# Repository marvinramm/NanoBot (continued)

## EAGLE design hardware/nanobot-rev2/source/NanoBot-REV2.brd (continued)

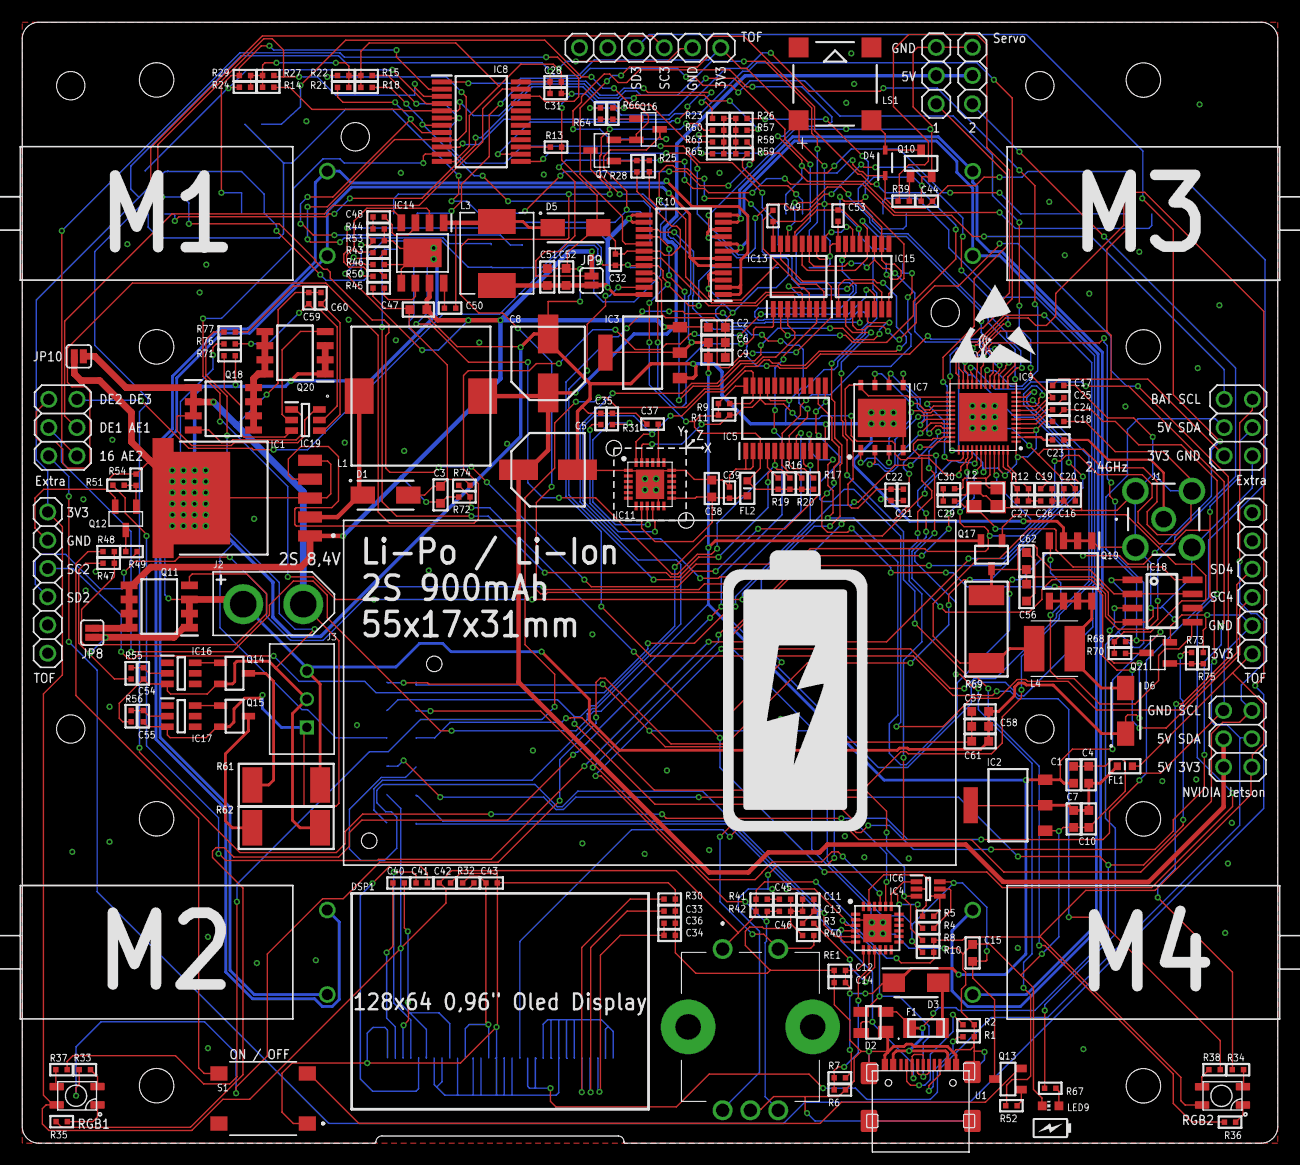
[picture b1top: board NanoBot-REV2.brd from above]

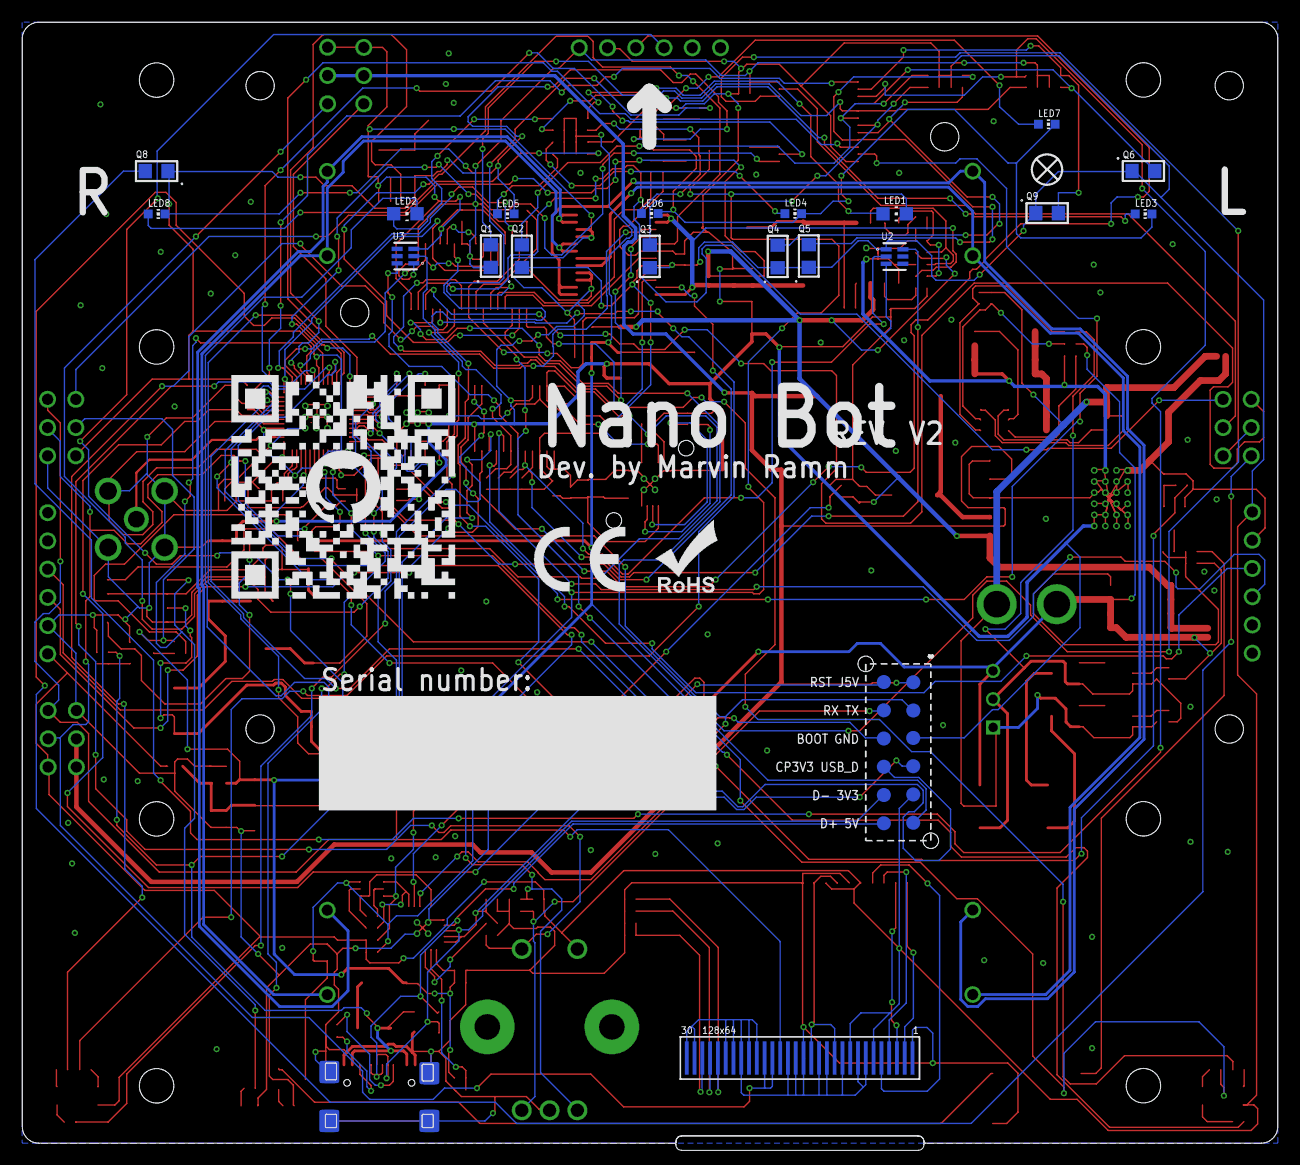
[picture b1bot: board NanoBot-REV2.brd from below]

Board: 2 copper layers, 112.9 x 100.8 mm, 240 parts (31 on the bottom side), 173 nets.

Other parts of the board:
U$3: JETSON_NANO

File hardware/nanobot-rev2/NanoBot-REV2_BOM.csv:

designators,description,manufacturer_part,lcsc_part,qty_per_board,link
U1,USB Connector,TYPE-C-31-M-31,C2760486,1,https://www.lcsc.com/product-detail/USB-Connectors_Korean-Hr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
F1,6V 1.5A 100A 3A 1206 Resettable Fuse,TLC-NSMD150,C261956,1,https://www.lcsc.com/product-detail/Resettable-Fuses_span-st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
D3,30V 550mV@5A 5A DO-221AC Schottky Barrier Diode,SK53AFL-TP,C780074,1,
D2,ESD protection,SP0503BAHTG,C7074,1,https://www.lcsc.com/product-detail/TVS_Littelfuse-SP0503BAH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
IC2,Linear Voltage Regulators 1A 60dB@(120Hz),AMS1117-3.3,C347222,1,https://www.lcsc.com/product-detail/Linear-Voltage-Regulator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
"FL1, FL2",50mΩ ±25% 120Ω@100MHz 0603 Ferrite Beads ROHS,BLM18PG121SN1D,C14709,2,https://www.lcsc.com/product-detail/Ferrite-Beads_Murata-Ele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
IC3,1.4A Fixed 5V~5V Positive 18V SOT-223 Linear Voltage Regulators (LDO) ROHS,AMS1117-5.0,C473812,1,https://www.lcsc.com/product-detail/Linear-Voltage-Regulator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
"D1, D5, D6",40V Single 500mV@3A 3A SMA(DO-214AC) Schottky Barrier Diodes (SBD) ROHS,SS34A,C2886580,3,https://www.lcsc.com/product-detail/Schottky-Barrier-Diodes-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
IC1,TO-263-5 DC-DC Converters ROHS,LM2576S-5.0,C2920854,1,https://www.lcsc.com/product-detail/DC-DC-Converters_Minos-L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
IC5,TSSOP-24 Signal Switches / Encoders & Decoders / Multiplexers ROHS,TCA9548APWR,C130026,1,https://www.lcsc.com/product-detail/Signal-Switches-Encoders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
L1,"1.9A 100uH ±20% SMD,12.5x12.5mm Power Inductors ROHS",SLF12575T-101M1R9-PF,C81470,1,https://www.lcsc.com/product-detail/Power-Inductors_TDK-SLF1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
IC4,QFN-24-EP(4x4) USB ICs ROHS,CP2102N-A02-GQFN24R,C969151,1,https://www.lcsc.com/product-detail/USB-ICs_SILICON-LABS-CP2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
IC6,"40V 150mW 100@10mA,1V 200mA 2 NPN SC-88 Bipolar Transistors - BJT ROHS",LMBT3904DW1T1G,C131781,1,https://www.lcsc.com/product-detail/Bipolar-Transistors-BJT_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
IC8,SSOP-24-208mil Analog Switches / Multiplexers ROHS,CD74HC4067SM96,C98457,1,https://www.lcsc.com/product-detail/Analog-Switches-Multiple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
IC7,WSON-8-EP(5x6) NOR FLASH ROHS,W25Q128JVPIQ,C2803379,1,https://www.lcsc.com/product-detail/NOR-FLASH_Winbond-Elec-W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
J1,1 Inner bore SMA Board Edge Positive foot 6GHz -65℃~+165℃ 50Ω 6.35mm Plugin RF Connectors / Coaxial Connectors ROHS,5-1814832-2,C482015,1,https://www.lcsc.com/product-detail/RF-Connectors-Coaxial-Co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
IC9,QFN-48-EP(6x6) RF Transceiver ICs ROHS,ESP32-D0WDQ6,C129733,1,https://www.lcsc.com/product-detail/RF-Transceiver-ICs_Espre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
L2,40MHz 12pF ±10ppm SMD3225-4P Crystals ROHS,S3240000121040,C426989,1,https://www.lcsc.com/product-detail/Crystals_JGHC-S324000012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
"Q1, Q2, Q3, Q4, Q5, Q6, Q8, Q9",20mA NPN 30V 100nA 940nm 0805 Phototransistors ROHS,PT17-21C/L41/TR8,C100090,8,https://www.lcsc.com/product-detail/Phototransistors_Everlig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
"U2, U3",Ambient Light Sensors ROHS,TCS34725FN,C2649487,2,https://www.lcsc.com/product-detail/Ambient-Light-Sensors_Ad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
"Q7, Q12, Q16, Q21","20V 2.9A 57mΩ@4.5V,3.6A 710mW N Channel SOT-23 MOSFETs ROHS",SI2302DDS-T1-GE3,C194092,4,https://www.lcsc.com/product-detail/MOSFETs_Vishay-Intertech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
"LED1, LED2",2600K~3200K White light 80mW 0805 Light Emitting Diodes (LED) ROHS,BZ-C0805-W2-E1,C2833071,2,https://www.lcsc.com/product-detail/Light-Emitting-Diodes-LE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
IC10,1A Brush DC Motor 2.7V~5.5V Parallel SSOP-24 Motor Driver ICs ROHS,"TB6612FNG,C,8,EL",C141517,1,https://www.lcsc.com/product-detail/Motor-Driver-ICs_TOSHIBA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
IC11,QFN-24-EP(4x4) Attitude Sensor/Gyroscope ROHS,MPU-6050,C24112,1,https://www.lcsc.com/product-detail/Attitude-Sensor-Gyroscop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
RE1,Plugin Rotary Encoders ROHS,PEC12R-4120F-S0012,C143801,1,https://www.lcsc.com/product-detail/Rotary-Encoders_BOURNS-P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
LS1,"Externally Driven 85dB@3.6V,10cm Magnetic 3.6V 2731Hz SMD,7.5x7.5mm Buzzers ROHS",KLJ-7525-3627,C189208,1,https://www.lcsc.com/product-detail/Buzzers_KELIKING-KLJ-752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
D4,100V 400mW Single 1.25V@150mA 8ns 300mA SOD-323 Switching Diode ROHS,1N4148WS,C917117,1,https://www.lcsc.com/product-detail/Switching-Diode_JSMSEMI-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
"Q10, Q13","40V 200mW 100@10mA,1V 200mA NPN SOT-23 Bipolar Transistors - BJT ROHS",MMBT3904,C181119,2,https://www.lcsc.com/product-detail/Bipolar-Transistors-BJT_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
"IC13, IC15",2V~6V TSSOP-16 Shifting Register ROHS,"74HC595PW,118",C5948,2,https://www.lcsc.com/product-detail/Shifting-Register_Nexper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
Q11,SOP-8 MOSFETs ROHS,IRF7416TRPBF,C5350823,1,https://www.lcsc.com/product-detail/MOSFETs_TECH-PUBLIC-IRF7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
S1,"50mA SPST 24V SMD-4P,6x6.6mm Tactile Switches ROHS",B3S-1002P,C271751,1,https://www.lcsc.com/product-detail/Tactile-Switches_Omron-E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
IC14,,MP1584EN-LF-Z,,1,
L3,"8.8A 4.7uH ±20% 8.8A 20.8mΩ SMD,6.6x7.3mm Inductors (SMD) ROHS",MDA7050-4R7M,C2847541,1,https://www.lcsc.com/product-detail/Inductors-SMD_KOHERelec-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
"LED3, LED4, LED5, LED6, LED7, LED8",White light 100mW 0603 Light Emitting Diodes (LED) ROHS,SZYY0603W,C434422,6,https://www.lcsc.com/product-detail/Light-Emitting-Diodes-LE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
"Q14, Q15","20V 2.5A 1000mW 55mΩ@4.5V,3.6A N Channel SOT-23 MOSFETs ROHS",FSS2302S,C2926140,2,https://www.lcsc.com/product-detail/MOSFETs_FOSAN-FSS2302S_C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
"IC16, IC17",SOT-23-6 Battery Management ICs ROHS,HY2213-BB3A,C113632,2,https://www.lcsc.com/product-detail/Battery-Management-ICs_H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
J2,Power Connectors ROHS,XT30U-M,C99101,1,https://www.lcsc.com/product-detail/Power-Connectors_Changzh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
"Q18, Q20, Q19","30V 13A 3.1W 11.5mΩ@10V,12A N Channel SOIC-8 MOSFETs ROHS",AO4406AL,C35349,3,https://www.lcsc.com/product-detail/MOSFETs_Alpha-Omega-Semi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
IC19,SOT-23-6 Battery Management ICs ROHS,HY2120-CB,C116509,1,https://www.lcsc.com/product-detail/Battery-Management-ICs_H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
Q17,SOT-23-3L MOSFETs ROHS,AO3407A,C5379096,1,https://www.lcsc.com/product-detail/MOSFETs_MSKSEMI-AO3407A_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
L4,"1.6A 10uH ±20% 2A 106mΩ SMD,5x5mm Inductors (SMD) ROHS",LQH5BPB100MT0L,C521243,1,https://www.lcsc.com/product-detail/Inductors-SMD_Murata-Ele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
IC18,SOP-8 Battery Management ICs ROHS,CN3302,C559039,1,https://www.lcsc.com/product-detail/Battery-Management-ICs_S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
LED9,red led 0603,,,1,
"R1, R2, R14, R15, R18, R21, R22, R24, R27",5.1kΩ 0402,,,9,
"R9, R11, R4, R5, R10, R8, R13, R19, R16, R20, R17, R31, R32, R40, R41, R42, R50",10kΩ 0402,,,17,
"R3, R29, R33, R35, R37, R34, R36, R38, R71, R67",2.2kΩ 0402,,,10,
R7,22kΩ 0402,,,1,
R6,33kΩ 0402,,,1,
R12,20kΩ 0402,,,1,
"R23, R26, R57, R58, R59, R60, R63, R65, R55, R56",100Ω 0402,,,10,
"R25, R39, R48, R49, R51, R52, R64, R70, R73",1kΩ 0402,,,9,
"R28, R47, R54, R46, R43, R44, R45, R66, R72, R68, R75",100kΩ 0402,,,11,
R30,390kΩ 0402,,,1,
R53,75kΩ 0402,,,1,
"R61, R62",62Ω 2512,,,2,
"R76, R77",330Ω 0402,,,2,
R74,64.9kΩ 0402,,,1,
R69,0.1Ω 2512,,,1,
"C1, C2",4.7uF 0603 16V,,,2,
"C4, C7, C10, C6, C9, C3, C15, C38, C47, C51, C52, C62, C56, C57, C58, C61",10uF 0603 16V,,,16,
"C5, C8","150uF 16V ±20% SMD,D6.3xL7.7mm Aluminum Electrolytic Capacitors - SMD ROHS",UUD1C151MCL1GS,C445270,2,https://www.lcsc.com/product-detail/Aluminum-Electrolytic-Ca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
"C11, C12, C28, C22, C17, C19, C18, C20, C32, C35, C49, C53, C50, C54, C55, C59, C60",0.1uF 0402 16V,,,17,
"C13, C14",4.7uF 0402 6.3V,,,2,
"C29, C30",12pF 0402,,,2,
C27,3nF 0402,,,1,
"C26, C37, C45, C46",10nF 0402,,,4,
C23,5.6pF 0402,,,1,
"C24, C25",270pF 0420,,,2,
"C21, C31, C39, C33, C34, C36, C40, C41, C42, C43, C44",1uF 0402 16V,,,11,
"C16, C48",100pF 0402,,,2,
